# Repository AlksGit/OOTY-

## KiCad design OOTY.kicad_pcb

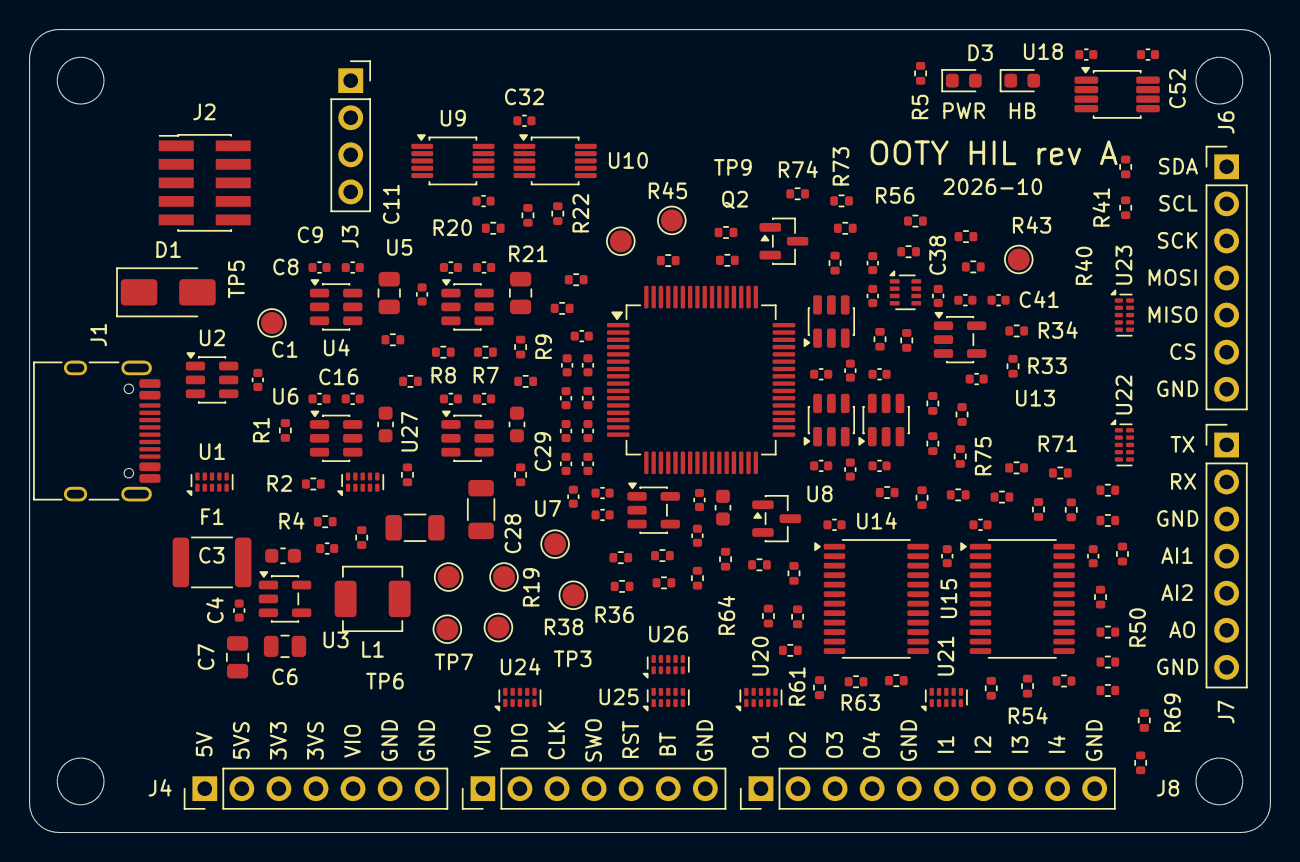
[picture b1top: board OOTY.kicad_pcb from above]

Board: 4 copper layers, 85.0 x 55.0 mm, 185 parts (0 on the bottom side), 118 nets, no tracks yet.

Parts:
C1, C2, C4, C8, C9, C11, C12, C14, C15, C17, C18, C20, C21, C22, C23, C25, C28, C30, C31, C32, C36, C43, C44, C45, C46, C47, C48, C49, C50, C51, C52, C53, C54: 100nF/50V; C_0402_1005Metric
C3, C16, C19: 10uF/10V; C_0603_1608Metric
C5: 6.8pF DNP; C_0402_1005Metric
C6, C7: 22uF/25V; C_0805_2012Metric
C10, C13: 10uF/25V; C_0805_2012Metric
C24: 4.7uF/16V; C_0603_1608Metric
C26, C33, C34, C35: 10nF/50V; C_0402_1005Metric
C27, C29, C37, C38, C39, C40, C41: 1uF/25V; C_0402_1005Metric
C42: 1nF/50V; C_0402_1005Metric
D1: SMAJ5.0A; D_SMA
D2: PWR; LED_0603_1608Metric
D3: HB; LED_0603_1608Metric
F1: PTC 2.6A; Fuse_1812_4532Metric
H1, H2, H3, H4: M3; MountingHole_3.2mm_M3
J1: TYPE-C-31-M-12; USB_C_Receptacle_HRO_TYPE-C-31-M-12
J2: SWD_HIL; PinHeader_2x05_P1.27mm_Vertical_SMD
J3: OLED 0.91in; PinSocket_1x04_P2.54mm_Vertical
J4: J_PWR; PinHeader_1x07_P2.54mm_Vertical
J5: J_DBG; PinHeader_1x07_P2.54mm_Vertical
J6: J_BUS; PinHeader_1x07_P2.54mm_Vertical
J7: J_UART_ANA; PinHeader_1x07_P2.54mm_Vertical
J8: J_IO; PinHeader_1x10_P2.54mm_Vertical
L1: 2.2uH; L_Changjiang_FXL0420
Q1, Q2: 2N7002; SOT-23
R1, R2: 5.1k; R_0402_1005Metric
R3, R8, R13, R23, R24, R25, R26, R27, R28, R32, R36, R38, R39, R45, R46: 100k; R_0402_1005Metric
R4, R6, R31: 22k; R_0402_1005Metric
R5, R17: 1k; R_0402_1005Metric
R7, R10, R12, R15, R16, R22, R30, R37, R44: 10k; R_0402_1005Metric
R9, R11: 39k; R_0402_1005Metric
R14: 68k; R_0402_1005Metric
R18: 50mR 1% 1W; R_1206_3216Metric
R19: 100mR 1% 1W; R_1206_3216Metric
R20, R21: 2.2k; R_0402_1005Metric
R29, R57, R58, R59, R60, R61, R62, R63, R64, R65, R66, R67, R68, R69, R70, R71, R72, R73, R74, R75: 100R; R_0402_1005Metric
R33: 30k; R_0402_1005Metric
R34: 24k; R_0402_1005Metric
R35: 16k; R_0402_1005Metric
R40, R41, R42, R43: 4.7k; R_0402_1005Metric
R47, R48, R49, R50, R51, R52, R53, R54, R55, R56: 1M; R_0402_1005Metric
TP1: VBUS; TestPoint_Pad_D1.5mm
TP2: +5V; TestPoint_Pad_D1.5mm
TP3: +3V3; TestPoint_Pad_D1.5mm
TP4: 5V_SW; TestPoint_Pad_D1.5mm
TP5: 5V_DUT; TestPoint_Pad_D1.5mm
TP6: 3V3_SW; TestPoint_Pad_D1.5mm
TP7: 3V3_DUT; TestPoint_Pad_D1.5mm
TP8: GND; TestPoint_Pad_D1.5mm
TP9: BOOT0; TestPoint_Pad_D1.5mm
TP10: VIO; TestPoint_Pad_D1.5mm
U1, U20, U21, U22, U23, U24, U25, U26, U27: TPD4E05U06DQAR; USON-10_2.5x1.0mm_P0.5mm
U2: USBLC6-2SC6; SOT-23-6
U3: TLV62569DBVR; SOT-23-5
U4, U5, U6, U7: AP22653W6-7; SOT-23-6
U8: STM32G431RBT6; LQFP-64_10x10mm_P0.5mm
U9, U10: INA226AIDGSR; MSOP-10_3x3mm_P0.5mm
U11: TLV9001IDBVR; SOT-23-5
U12: TPS2116DRLR; SOT-583-8
U13: AP2127K-ADJTRG1; SOT-23-5
U14, U15: SN74LVC8T245PWR; TSSOP-24_4.4x7.8mm_P0.65mm
U16, U17, U19: SN74LVC1T45DBVR; SOT-23-6
U18: TCA9517ADGKR; VSSOP-8_3x3mm_P0.65mm

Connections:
3V3_DUT: C18.1, C19.1, J4.3, TP7.1, U7.6, U27.4
3V3_SW: J4.4, R19.2, TP6.1, U10.9, U27.5
3V3_SW_PRE: C15.1, C16.1, R19.1, U6.6, U10.8, U10.10
5V_DUT: C12.1, C13.1, J4.1, TP5.1, U5.6, U27.1
5V_SW: J4.2, R18.2, TP4.1, U9.9, U27.2
5V_SW_PRE: C9.1, C10.1, R18.1, U4.6, U9.8, U9.10
+3V3: C5.1, C6.1, C7.1, C14.1, C17.1, C20.1, C21.1, C22.1, C23.1, C24.1, C25.1, C26.1, C27.1, C28.1, C29.1, C31.1, C32.1, C36.1, C43.1, C45.1, C47.1, C49.1, C52.1, C53.1, J2.1, J3.2, L1.2, R3.1, R5.1, R7.2, R10.2, R12.2, R15.2, R20.2, R21.2, R22.2, R37.2, R42.2, R43.2, TP3.1, U6.1, U7.1, U7.3, U8.1, U8.16, U8.28, U8.29, U8.32, U8.48, U8.64, U9.6, U10.2, U10.6, U11.5, U14.1, U14.2, U15.1, U16.1, U17.1, U18.8, U19.1
+5V: C2.1, C3.1, C4.1, C8.1, C11.1, C37.1, C40.1, F1.2, R30.1, TP2.1, U3.1, U3.4, U4.1, U5.1, U5.3, U12.3, U13.1, U13.3
/connectors/BOOT: J5.6, R75.2, U25.1
/connectors/IN1: J8.6, R65.2, U21.1
/connectors/IN2: J8.7, R66.2, U21.2
/connectors/IN3: J8.8, R67.2, U21.4
/connectors/IN4: J8.9, R68.2, U21.5
/connectors/OUT1: J8.1, R57.2, U20.1
/connectors/OUT2: J8.2, R58.2, U20.2
/connectors/OUT3: J8.3, R59.2, U20.4
/connectors/OUT4: J8.4, R60.2, U20.5
/connectors/RESET: J5.5, R74.2, U24.5
/connectors/RX: J7.2, R69.2, U22.2
/connectors/SPI_CS: J6.6, R64.2, U23.2
/connectors/SPI_MISO: J6.5, R70.2, U23.1
/connectors/SPI_MOSI: J6.4, R63.2, U22.5
/connectors/SPI_SCK: J6.3, R62.2, U22.4
/connectors/SWCLK: J5.3, R72.2, U24.2
/connectors/SWDIO: J5.2, R73.2, U24.1
/connectors/SWO: J5.4, R71.2, U24.4
/connectors/TX: J7.1, R61.2, U22.1
/mcu/BOOT0: R16.1, TP9.1, U8.61
/mcu/LED_HB: R17.1, U8.44
/mcu/LED_HB_A: D3.2, R17.2
/mcu/NRST: C30.1, J2.10, U8.7
/mcu/SWCLK_HIL: J2.4, U8.50
/mcu/SWDIO_HIL: J2.2, U8.49
/mcu/SWO_HIL: J2.6, U8.56
/power/FB_3V3: C5.2, R3.2, R4.1, U3.5
/power/ILIM_3V3: R14.1, U7.5
/power/ILIM_3V3SW: R11.1, U6.5
/power/ILIM_5V: R9.1, U5.5
/power/ILIM_5VSW: R6.1, U4.5
/power/LED_PWR_A: D2.2, R5.2
/power/SW_3V3: L1.1, U3.3
/sensing/AOUT_BUF: R29.1, U11.1, U11.4
/vio/VIO_ADJ: C42.2, R33.2, R34.1, R35.1, U13.4
/vio/VIO_LDO: C38.1, C41.1, C42.1, R33.1, U12.6, U13.5
/vio/VSEL_D: Q1.3, R35.2
AIN1: J7.4, R23.1, U25.2
AIN1_ADC: C33.1, R23.2, R24.1, U8.8
AIN2: J7.5, R25.1, U25.4
AIN2_ADC: C34.1, R25.2, R26.1, U8.9
AOUT: J7.6, R29.2, U25.5
BOOT_B: R53.1, R75.1, U19.4
BOOT_DIR: R46.1, U8.57, U19.5
BOOT_DUT_CTL: U8.39, U19.3
CC1: J1.A5, R1.1, U1.1, U8.10
CC2: J1.B5, R2.1, U1.2, U8.11
DAC_OUT: U8.18, U11.3
EN_3V3SW: R13.1, U6.3, U8.3
EN_5VSW: R8.1, U4.3, U8.2
FAULT_3V3: R15.1, U7.4, U8.58
FAULT_3V3SW: R12.1, U6.4, U8.5
FAULT_5V: R10.1, U5.4, U8.6
FAULT_5VSW: R7.1, U4.4, U8.4
GND: C1.2, C2.2, C3.2, C4.2, C6.2, C7.2, C8.2, C9.2, C10.2, C11.2, C12.2, C13.2, C14.2, C15.2, C16.2, C17.2, C18.2, C19.2, C20.2, C21.2, C22.2, C23.2, C24.2, C25.2, C26.2, C27.2, C28.2, C29.2, C30.2, C31.2, C32.2, C33.2, C34.2, C35.2, C36.2, C37.2, C38.2, C39.2, C40.2, C41.2, C43.2, C44.2, C45.2, C46.2, C47.2, C48.2, C49.2, C50.2, C51.2, C52.2, C53.2, C54.2, D1.2, D2.1, D3.1, J1.A1, J1.A12, J1.B1, J1.B12, J1.SH, J2.3, J2.5, J2.9, J3.1, J4.6, J4.7, J5.7, J6.7, J7.3, J7.7, J8.5, J8.10, Q1.2, Q2.2, R1.2, R2.2, R4.2, R6.2, R8.2, R9.2, R11.2, R13.2, R14.2, R16.2, R24.2, R26.2, R28.2, R31.2, R32.2, R34.2, R36.2, R38.2, R39.2, R44.2, R45.2, R46.2, R47.2, R48.2, R49.2, R50.2, R51.2, R52.2, R53.2, TP8.1, U1.3, U1.8, U2.2, U3.2, U4.2, U5.2, U6.2, U7.2, U8.15, U8.27, U8.31, U8.47, U8.63, U9.1, U9.2, U9.7, U10.1, U10.7, U11.2, U12.1, U13.2, U14.11, U14.12, U14.13, U15.2, U15.11, U15.12, U15.13, U15.14, U16.2, U17.2, U18.4, U19.2, U20.3, U20.8, U21.3, U21.8, U22.3, U22.8, U23.3, U23.8, U24.3, U24.8, U25.3, U25.8, U26.3, U26.8, U27.3, U27.8
I2C_DUT_EN: R44.1, U8.59, U18.5
I2C_DUT_SCL_MCU: R42.1, U8.40, U18.7
I2C_DUT_SDA_MCU: R43.1, U8.41, U18.6
I2C_INT_SCL: J3.3, R21.1, U8.51, U9.5, U10.5
I2C_INT_SDA: J3.4, R20.1, U8.60, U9.4, U10.4
I2C_SCL: J6.2, R40.1, U18.2, U23.5
I2C_SDA: J6.1, R41.1, U18.3, U23.4
IN1_B: R47.1, R65.1, U15.21
IN1_MCU: U8.52, U15.3
IN2_B: R48.1, R66.1, U15.20
IN2_MCU: U8.53, U15.4
IN3_B: R49.1, R67.1, U15.19
IN3_MCU: U8.54, U15.5
IN4_B: R50.1, R68.1, U15.18
IN4_MCU: U8.55, U15.6
INA_ALERT: R22.1, U8.62, U9.3, U10.3
LS_OE_N: R37.1, U8.43, U14.22, U15.22
OUT1_B: R57.1, U14.21
OUT1_MCU: U8.12, U14.3
OUT2_B: R58.1, U14.20
OUT2_MCU: U8.13, U14.4
OUT3_B: R59.1, U14.19
OUT3_MCU: U8.14, U14.5
OUT4_B: R60.1, U14.18
OUT4_MCU: U8.24, U14.6
RESET_DUT_CTL: Q2.1, R45.1, U8.38
RESET_OD: Q2.3, R74.1
SPI_CS_B: R64.1, U14.14
SPI_CS_MCU: U8.42, U14.10
SPI_MISO_B: R51.1, R70.1, U15.16
SPI_MISO_MCU: U8.20, U15.8
SPI_MOSI_B: R63.1, U14.15
SPI_MOSI_MCU: U8.21, U14.9
SPI_SCK_B: R62.1, U14.16
SPI_SCK_MCU: U8.19, U14.8
SWCLK_B: R52.1, R72.1, U16.4
SWCLK_DIR: R38.1, U8.26, U16.5
SWCLK_MCU: U8.35, U16.3
SWDIO_B: R56.1, R73.1, U17.4
SWDIO_DIR: R39.1, U8.34, U17.5
SWDIO_MCU: U8.37, U17.3
SWO_DUT_B: R55.1, R71.1, U15.15
SWO_DUT_MCU: U8.17, U15.9
UART_RX_B: R54.1, R69.1, U15.17
UART_RX_MCU: U8.33, U15.7
UART_TX_B: R61.1, U14.17
UART_TX_MCU: U8.30, U14.7
USB_DM: J1.A7, J1.B7, U2.3, U2.4, U8.45
USB_DP: J1.A6, J1.B6, U2.1, U2.6, U8.46
VBUS: C1.1, D1.1, F1.1, J1.A4, J1.A9, J1.B4, J1.B9, TP1.1, U2.5
VIO: C39.1, C44.1, C46.1, C48.1, C50.1, C51.1, C54.1, J4.5, J5.1, R27.1, R40.2, R41.2, R54.2, R55.2, R56.2, TP10.1, U12.2, U12.7, U14.23, U14.24, U15.23, U15.24, U16.6, U17.6, U18.1, U19.6, U26.1
VIO_MODE: R32.1, U8.23, U12.5
VIO_MON: C35.1, R27.2, R28.1, U8.25
VIO_PR1: R30.2, R31.1, U8.22, U12.4
VIO_VSEL: Q1.1, R36.1, U8.36

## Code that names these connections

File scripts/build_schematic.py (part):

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    "VBAT": "+3V3", "VDD": "+3V3", "VDDA": "+3V3", "VREF+": "+3V3",
    "VSS": "GND", "VSSA": "GND",
    "PG10": "NRST", "PB8": "BOOT0",
    "PA11": "USB_DM", "PA12": "USB_DP",
    "PA13": "SWDIO_HIL", "PA14": "SWCLK_HIL", "PB3": "SWO_HIL",
    # Rail control and status
    "PC13": "EN_5VSW", "PC14": "EN_3V3SW",
    "PC15": "FAULT_5VSW", "PF0": "FAULT_3V3SW", "PF1": "FAULT_5V", "PB5": "FAULT_3V3",
    "PB9": "INA_ALERT",
    # Internal I2C1 (current monitors + OLED)
    "PA15": "I2C_INT_SCL", "PB7": "I2C_INT_SDA",
    # Analog
    "PA4": "DAC_OUT", "PC0": "AIN1_ADC", "PC1": "AIN2_ADC", "PC2": "CC1", "PC3": "CC2",
    "PB1": "VIO_MON",
    # VIO selection and translators
    "PC4": "VIO_PR1", "PC5": "VIO_MODE", "PB14": "VIO_VSEL", "PA9": "LS_OE_N",
    "PB6": "I2C_DUT_EN",
    # DUT digital I/O
    "PA0": "OUT1_MCU", "PA1": "OUT2_MCU", "PA2": "OUT3_MCU", "PB0": "OUT4_MCU",
    "PC10": "IN1_MCU", "PC11": "IN2_MCU", "PC12": "IN3_MCU", "PD2": "IN4_MCU",
    # DUT UART (USART3), SPI (SPI1), I2C (I2C3)
    "PB10": "UART_TX_MCU", "PB11": "UART_RX_MCU",
    "PA5": "SPI_SCK_MCU", "PA6": "SPI_MISO_MCU", "PA7": "SPI_MOSI_MCU", "PA8": "SPI_CS_MCU",
    "PC8": "I2C_DUT_SCL_MCU", "PC9": "I2C_DUT_SDA_MCU",
    # DUT SWD probe (SWO captured by USART2_RX)
    "PB13": "SWCLK_MCU", "PB15": "SWDIO_MCU", "PB2": "SWCLK_DIR", "PB12": "SWDIO_DIR",
    "PA3": "SWO_DUT_MCU",
    # DUT RESET / BOOT open-drain drivers
    "PC6": "RESET_DUT_CTL", "PC7": "BOOT_DUT_CTL",
    "PA10": None,
    # BOOT_DIR is not on PB4: PB4 is NJTRST with a 25-55k pull-up after reset (DS12589 Table 12,
    # note 4), which beat the 100k pull-down and drove the DUT BOOT pin during HIL resets.
    "PD10": "BOOT_DIR", "PB4": None,
    # Fixed DUT rails enable (pulled up: on by default)
    "PD8": "EN_5V", "PD9": "EN_3V3",
    # User buttons (active low) and heartbeat LED: pins on the side facing the top-right corner
    "PE11": "BTN1", "PE10": "BTN2", "PE12": "LED_HB",
    # Spare LQFP-80 GPIO
    "PE7": None, "PE8": None, "PE9": None, "PE13": None, "PE14": None, "PE15": None,
    "PD0": None, "PD1": None,
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    cap(sh, C1U, "+5V", near=(ldo, "VIN"))
    cap(sh, C1U, "VIO_LDO", near=(ldo, "VOUT"))
    res(sh, R30K, "VIO_LDO", "VIO_ADJ")
    sh.add("C", "Device:C", value_of(C1N), {"1": "VIO_LDO", "2": "VIO_ADJ"}, rot=90,
           fields={"LCSC": C1N})
    res(sh, R24K, "VIO_ADJ", "GND")
    res(sh, R16K, "VIO_ADJ", "VSEL_D")
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               fields={"Footprint": HOLE_FOOTPRINT})

    sh.note("Signal path: header -> TVS -> 100R series -> translator / circuit.")
    sh.note("DUT rails and VIO are probed on J_PWR / J_DBG pins (no separate test points).")
    return sh


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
